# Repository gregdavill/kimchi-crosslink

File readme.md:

# kimχ micro lid Crosslink-nx

This project is an add-on (lid) expansion board for the [kimχ micro i.MX8M Mini SBC](https://labs.groupgets.com/kimchi-micro).

This board is designed as a general purpose plotform for the Lattice Crosslink-nx FPGA, but it's main purpose is to investigate the options for converting the 4-lane MIPI-DSI signals from the Kimchi to a standard HDMI monitor.

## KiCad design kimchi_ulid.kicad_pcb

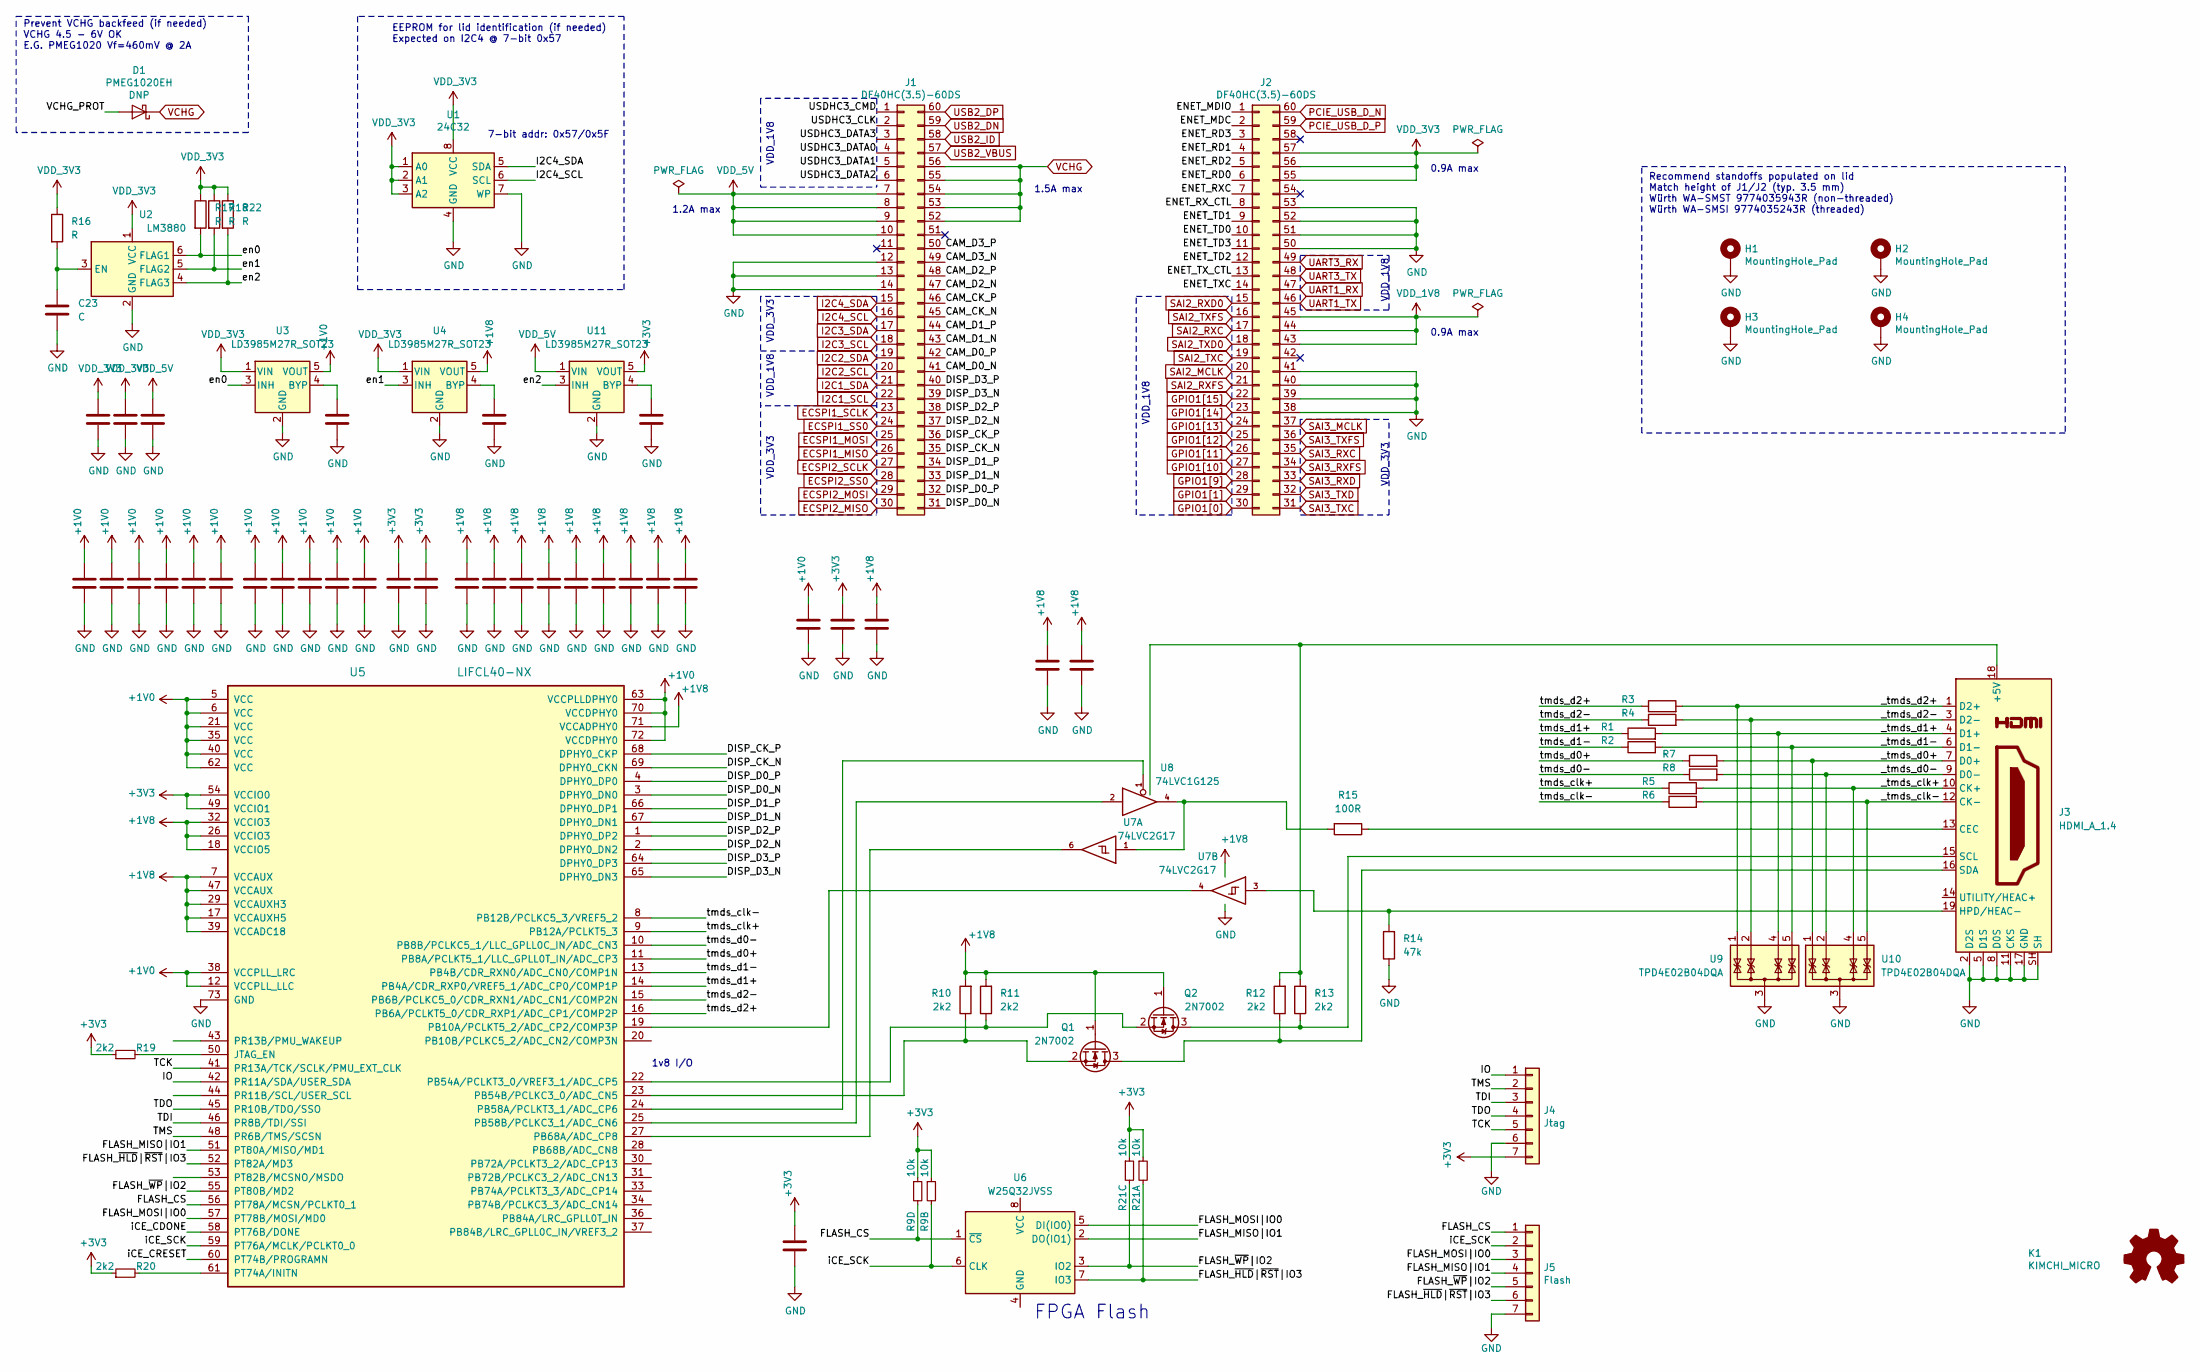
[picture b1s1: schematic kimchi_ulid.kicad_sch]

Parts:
C1, C2, C3, C4, C5, C6, C7, C8, C9, C10, C11, C12, C13, C14, C15, C16, C17, C18, C19, C20, C21, C22, C30, C34, C35: 0.1uF; C_0402_1005Metric
C23: C; C_0402_1005Metric
C24, C25, C26: 4.7uF; C_0603_1608Metric
C27, C28, C29: 0.01uF; C_0402_1005Metric
C31, C32, C33: 10uF; C_0603_1608Metric
D1: PMEG1020EH; D_SOD-123F
H1, H2, H3, H4: MountingHole_Pad; MountingHole_M2_Standoff; Mfgrpart 9774035943R
J1, J2: DF40HC(3.5)-60DS
J3: HDMI_A_1.4; HDMI-10029449-111RLF
J4: Jtag; PinHeader_1x07_P2.54mm_Vertical
J5: Flash; PinHeader_1x07_P2.54mm_Vertical
K1: KIMCHI_MICRO
LOGO1: Logo_Open_Hardware_Small; OSHW-Logo_5.7x6mm_SilkScreen
Q1, Q2: 2N7002; SOT-23
R1, R2, R3, R4, R5, R6, R7, R8, R16: R; R_0402_1005Metric
R9, R21: 10k; R_Array_Convex_4x0402
R10, R11, R12, R13: 2k2; R_0402_1005Metric
R14: 47k; R_0402_1005Metric
R15: 100R; R_0402_1005Metric
R17, R18, R22: R
R19, R20: 2k2; R_0402
U1: 24C32; DFN-8-1EP_3x2mm_P0.5mm_EP1.36x1.46mm; Part M24C32-FMC6TG
U2: LM3880; SOT-23-6
U3, U4, U11: LD3985M27R_SOT23; SOT-23-5
U5: LIFCL40-NX; QFN-72-1EP_10x10mm_P0.5mm_EP6x6mm
U6: W25Q32JVSS; SOIC-8_5.23x5.23mm_P1.27mm
U7: 74LVC2G17; SOT-23-6
U8: 74LVC1G125; SOT-23-5
U9, U10: TPD4E02B04DQA; USON-10_2.5x1.0mm_P0.5mm

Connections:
+1V0: C1.1, C2.1, C3.1, C4.1, C5.1, C6.1, C7.1, C8.1, C9.1, C10.1, C22.1, C31.1, U3.5 (VOUT), U5.5 (VCC), U5.6 (VCC), U5.12 (VCCPLL_LLC), U5.21 (VCC), U5.35 (VCC), U5.38 (VCCPLL_LRC), U5.40 (VCC), U5.62 (VCC), U5.63 (VCCPLLDPHY0), U5.70 (VCCDPHY0), U5.72 (VCCDPHY0)
+1V8: C13.1, C14.1, C15.1, C16.1, C17.1, C18.1, C19.1, C20.1, C21.1, C33.1, C34.1, C35.1, Q1.1 (G), Q2.1 (G), R10.2, R11.2, U4.5 (VOUT), U5.7 (VCCAUX), U5.17 (VCCAUXH5), U5.18 (VCCIO5), U5.26 (VCCIO3), U5.29 (VCCAUXH3), U5.32 (VCCIO3), U5.39 (VCCADC18), U5.47 (VCCAUX), U5.71 (VCCADPHY0), U7.5 (VCC)
+3V3: C11.1, C12.1, C30.1, C32.1, J4.7, R9.3, R9.7, R20.1, R21.1, R21.5, U5.49 (VCCIO1), U5.54 (VCCIO0), U11.5 (VOUT)
/CAM_CK_N: J1.45
/CAM_CK_P: J1.46
/CAM_D0_N: J1.41
/CAM_D0_P: J1.42
/CAM_D1_N: J1.43
/CAM_D1_P: J1.44
/CAM_D2_N: J1.47
/CAM_D2_P: J1.48
/CAM_D3_N: J1.49
/CAM_D3_P: J1.50
/DISP_CK_N: J1.35, U5.69 (DPHY0_CKN)
/DISP_CK_P: J1.36, U5.68 (DPHY0_CKP)
/DISP_D0_N: J1.31, U5.3 (DPHY0_DN0)
/DISP_D0_P: J1.32, U5.4 (DPHY0_DP0)
/DISP_D1_N: J1.33, U5.67 (DPHY0_DN1)
/DISP_D1_P: J1.34, U5.66 (DPHY0_DP1)
/DISP_D2_N: J1.37, U5.2 (DPHY0_DN2)
/DISP_D2_P: J1.38, U5.1 (DPHY0_DP2)
/DISP_D3_N: J1.39, U5.65 (DPHY0_DN3)
/DISP_D3_P: J1.40, U5.64 (DPHY0_DP3)
/ENET_MDC: J2.2
/ENET_MDIO: J2.1
/ENET_RD0: J2.6
/ENET_RD1: J2.4
/ENET_RD2: J2.5
/ENET_RD3: J2.3
/ENET_RXC: J2.7
/ENET_RX_CTL: J2.8
/ENET_TD0: J2.10
/ENET_TD1: J2.9
/ENET_TD2: J2.12
/ENET_TD3: J2.11
/ENET_TXC: J2.14
/ENET_TX_CTL: J2.13
/FLASH_CS: J5.1, R9.8, U5.56 (PT78A/MCSN/PCLKT0_1), U6.1 (~CS)
/FLASH_MISO|IO1: J5.4, U5.51 (PT80A/MISO/MD1), U6.2 (DO(IO1))
/FLASH_MOSI|IO0: J5.3, U5.57 (PT78B/MOSI/MD0), U6.5 (DI(IO0))
/FLASH_~HLD|~RST|IO3: J5.6, R21.2, U5.52 (PT82A/MD3), U6.7 (IO3)
/FLASH_~WP|IO2: J5.5, R21.6, U5.55 (PT80B/MD2), U6.3 (IO2)
/IO: J4.1, U5.42 (PR11A/SDA/USER_SDA)
/TCK: J4.5, U5.41 (PR13A/TCK/SCLK/PMU_EXT_CLK)
/TDI: J4.3, U5.46 (PR8B/TDI/SSI)
/TDO: J4.4, U5.45 (PR10B/TDO/SSO)
/TMS: J4.2, U5.48 (PR6B/TMS/SCSN)
/USDHC3_CLK: J1.2
/USDHC3_CMD: J1.1
/USDHC3_DATA0: J1.4
/USDHC3_DATA1: J1.5
/USDHC3_DATA2: J1.6
/USDHC3_DATA3: J1.3
/VCHG_PROT: D1.2 (A)
/_tmds_clk+: J3.10 (CK+), R5.2, U10.4 (IO3)
/_tmds_clk-: J3.12 (CK-), R6.2, U10.5 (IO4)
/_tmds_d0+: J3.7 (D0+), R7.2, U10.1 (IO1)
/_tmds_d0-: J3.9 (D0-), R8.2, U10.2 (IO2)
/_tmds_d1+: J3.4 (D1+), R1.2, U9.4 (IO3)
/_tmds_d1-: J3.6 (D1-), R2.2, U9.5 (IO4)
/_tmds_d2+: J3.1 (D2+), R3.2, U9.1 (IO1)
/_tmds_d2-: J3.3 (D2-), R4.2, U9.2 (IO2)
/en0: R17.2, U2.6 (FLAG1), U3.3 (INH)
/en1: R18.2, U2.5 (FLAG2), U4.3 (INH)
/en2: R22.2, U2.4 (FLAG3), U11.3 (INH)
/iCE_CDONE: U5.58 (PT76B/DONE)
/iCE_CRESET: U5.60 (PT74B/PROGRAMN)
/iCE_SCK: J5.2, R9.4, U5.59 (PT76A/MCLK/PCLKT0_0), U6.6 (CLK)
/tmds_clk+: R5.1, U5.9 (PB12A/PCLKT5_3)
/tmds_clk-: R6.1, U5.8 (PB12B/PCLKC5_3/VREF5_2)
/tmds_d0+: R7.1, U5.11 (PB8A/PCLKT5_1/LLC_GPLL0T_IN/ADC_CP3)
/tmds_d0-: R8.1, U5.10 (PB8B/PCLKC5_1/LLC_GPLL0C_IN/ADC_CN3)
/tmds_d1+: R1.1, U5.14 (PB4A/CDR_RXP0/VREF5_1/ADC_CP0/COMP1P)
/tmds_d1-: R2.1, U5.13 (PB4B/CDR_RXN0/ADC_CN0/COMP1N)
/tmds_d2+: R3.1, U5.16 (PB6A/PCLKT5_0/CDR_RXP1/ADC_CP1/COMP2P)
/tmds_d2-: R4.1, U5.15 (PB6B/PCLKC5_0/CDR_RXN1/ADC_CN1/COMP2N)
ECSPI1_MISO: J1.26
ECSPI1_MOSI: J1.25
ECSPI1_SCLK: J1.23
ECSPI1_SS0: J1.24
ECSPI2_MISO: J1.30
ECSPI2_MOSI: J1.29
ECSPI2_SCLK: J1.27
ECSPI2_SS0: J1.28
GND: C1.2, C2.2, C3.2, C4.2, C5.2, C6.2, C7.2, C8.2, C9.2, C10.2, C11.2, C12.2, C13.2, C14.2, C15.2, C16.2, C17.2, C18.2, C19.2, C20.2, C21.2, C22.2, C23.2, C24.2, C25.2, C26.2, C27.2, C28.2, C29.2, C30.2, C31.2, C32.2, C33.2, C34.2, C35.2, H1.1, H2.1, H3.1, H4.1, J1.12, J1.13, J1.14, J2.38, J2.39, J2.40, J2.41, J2.50, J2.51, J2.52, J2.53, J3.2 (D2S), J3.5 (D1S), J3.8 (D0S), J3.11 (CKS), J3.17 (GND), J3.SH, J4.6, J5.7, R14.1, U1.4 (GND), U1.7 (WP), U2.2 (GND), U3.2 (GND), U4.2 (GND), U5.73 (GND), U7.2 (GND), U8.3 (GND), U9.3 (G), U9.8 (G), U10.3 (G), U10.8 (G), U11.2 (GND)
GPIO1[0]: J2.30
GPIO1[1]: J2.29
GPIO1[9]: J2.28
GPIO1[10]: J2.27
GPIO1[11]: J2.26
GPIO1[12]: J2.25
GPIO1[13]: J2.24
GPIO1[14]: J2.23
GPIO1[15]: J2.22
I2C1_SCL: J1.22
I2C1_SDA: J1.21
I2C2_SCL: J1.20
I2C2_SDA: J1.19
I2C3_SCL: J1.18
I2C3_SDA: J1.17
I2C4_SCL: J1.16, U1.6 (SCL)
I2C4_SDA: J1.15, U1.5 (SDA)
unnamed: C23.1, R16.2, U2.3 (EN)
unnamed: C27.1, U3.4 (BYP)
unnamed: C28.1, U4.4 (BYP)
unnamed: C29.1, U11.4 (BYP)
unnamed: J3.13 (CEC), R15.1
unnamed: J3.15 (SCL), Q2.3 (D), R13.1
unnamed: J3.16 (SDA), Q1.3 (D), R12.1
unnamed: J3.19 (HPD/HEAC-), R14.2, U7.3
unnamed: Q1.2 (S), R10.1, U5.23 (PB54B/PCLKC3_0/ADC_CN5)
unnamed: Q2.2 (S), R11.1, U5.22 (PB54A/PCLKT3_0/VREF3_1/ADC_CP5)
unnamed: R15.2, U7.1, U8.4
unnamed: R19.2, U5.50 (JTAG_EN)
unnamed: R20.2, U5.61 (PT74A/INITN)
unnamed: U5.19 (PB10A/PCLKT5_2/ADC_CP2/COMP3P), U7.4
unnamed: U5.24 (PB58A/PCLKT3_1/ADC_CP6), U8.1
unnamed: U5.25 (PB58B/PCLKC3_1/ADC_CN6), U8.2
unnamed: U5.27 (PB68A/ADC_CP8), U7.6
PCIE_USB_D_N: J2.60
PCIE_USB_D_P: J2.59
SAI2_MCLK: J2.20
SAI2_RXC: J2.17
SAI2_RXD0: J2.15
SAI2_RXFS: J2.21
SAI2_TXC: J2.19
SAI2_TXD0: J2.18
SAI2_TXFS: J2.16
SAI3_MCLK: J2.37
SAI3_RXC: J2.35
SAI3_RXD: J2.33
SAI3_RXFS: J2.34
SAI3_TXC: J2.31
SAI3_TXD: J2.32
SAI3_TXFS: J2.36
UART1_RX: J2.47
UART1_TX: J2.46
UART3_RX: J2.49
UART3_TX: J2.48
USB2_DN: J1.59
USB2_DP: J1.60
USB2_ID: J1.58
USB2_VBUS: J1.57
VCHG: D1.1 (K), J1.52, J1.53, J1.54, J1.55, J1.56
VDD: J3.18 (+5V), R12.2, R13.2, U8.5 (VDD)
VDD_1V8: J2.43, J2.44, J2.45
VDD_3V3: C24.1, C25.1, J2.55, J2.56, J2.57, R16.1, R17.1, R18.1, R22.1, U1.1 (A0), U1.2 (A1), U1.3 (A2), U1.8 (VCC), U2.1 (VCC), U3.1 (VIN), U4.1 (VIN)
VDD_5V: C26.1, J1.7, J1.8, J1.9, J1.10, U11.1 (VIN)

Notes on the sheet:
Prevent VCHG backfeed (if needed) VCHG 4.5 - 6V OK E.G. PMEG1020 Vf=460mV @ 2A
EEPROM for lid identification (if needed) Expected on I2C4 @ 7-bit 0x57
7-bit addr: 0x57/0x5F
1v8 I/O
1.2A max
VDD_1V8
VDD_3V3
1.5A max
FPGA Flash
0.9A max
Recommend standoffs populated on lid Match height of J1/J2 (typ. 3.5 mm) Würth WA-SMST 9774035943R (non-threaded) Würth WA-SMSI 9774035243R (threaded)

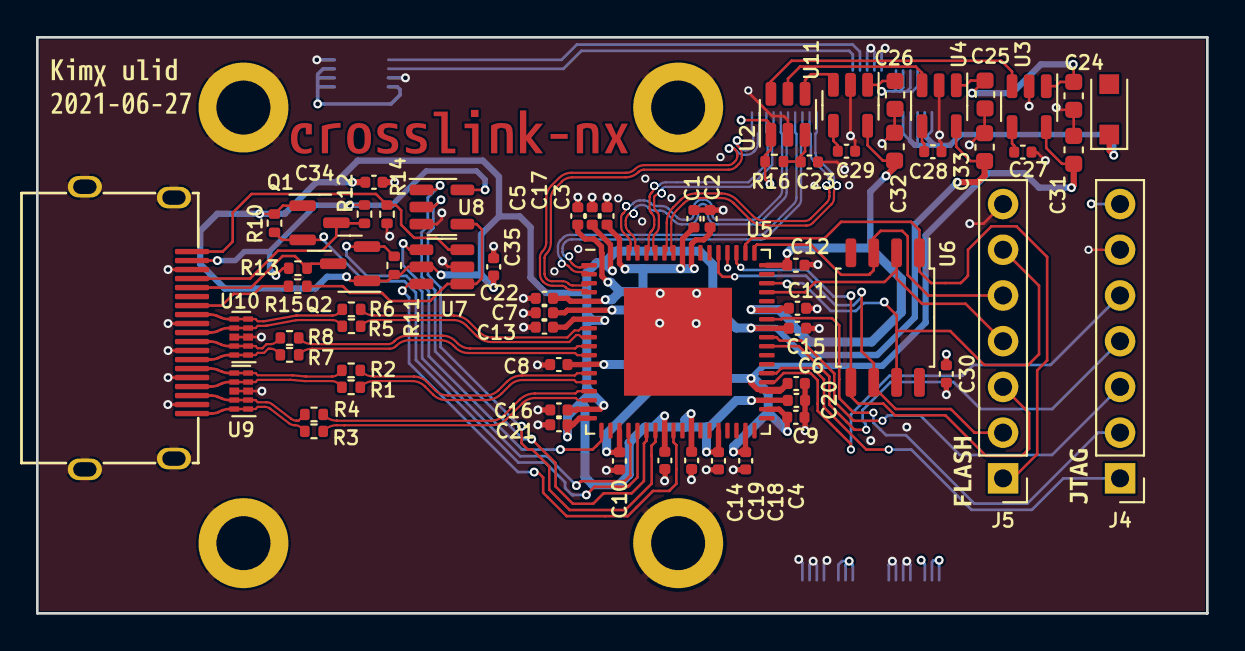
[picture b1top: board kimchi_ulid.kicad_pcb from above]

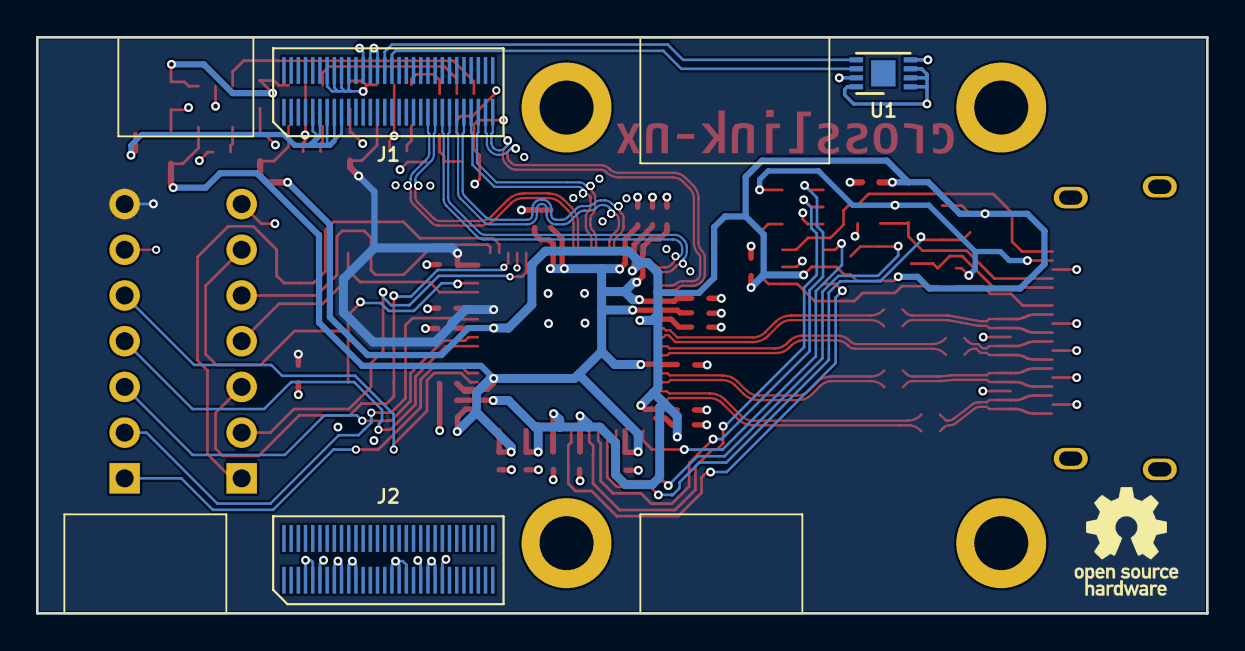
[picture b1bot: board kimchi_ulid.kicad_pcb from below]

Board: 4 copper layers, 65.0 x 32.0 mm, 80 parts (9 on the bottom side), 66 nets.

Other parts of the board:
svg2mod, svg2mod#2, svg2mod#3, svg2mod#4, svg2mod#5: G***; svg2mod

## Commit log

2021-06-27 Initial work on design
    - Update symbols to KiCad v6
    - Start inital placement and routing of design
2021-06-27 Update routing
2021-07-03 Update
    - Complete inital routing
    - Render a board view and update readme
